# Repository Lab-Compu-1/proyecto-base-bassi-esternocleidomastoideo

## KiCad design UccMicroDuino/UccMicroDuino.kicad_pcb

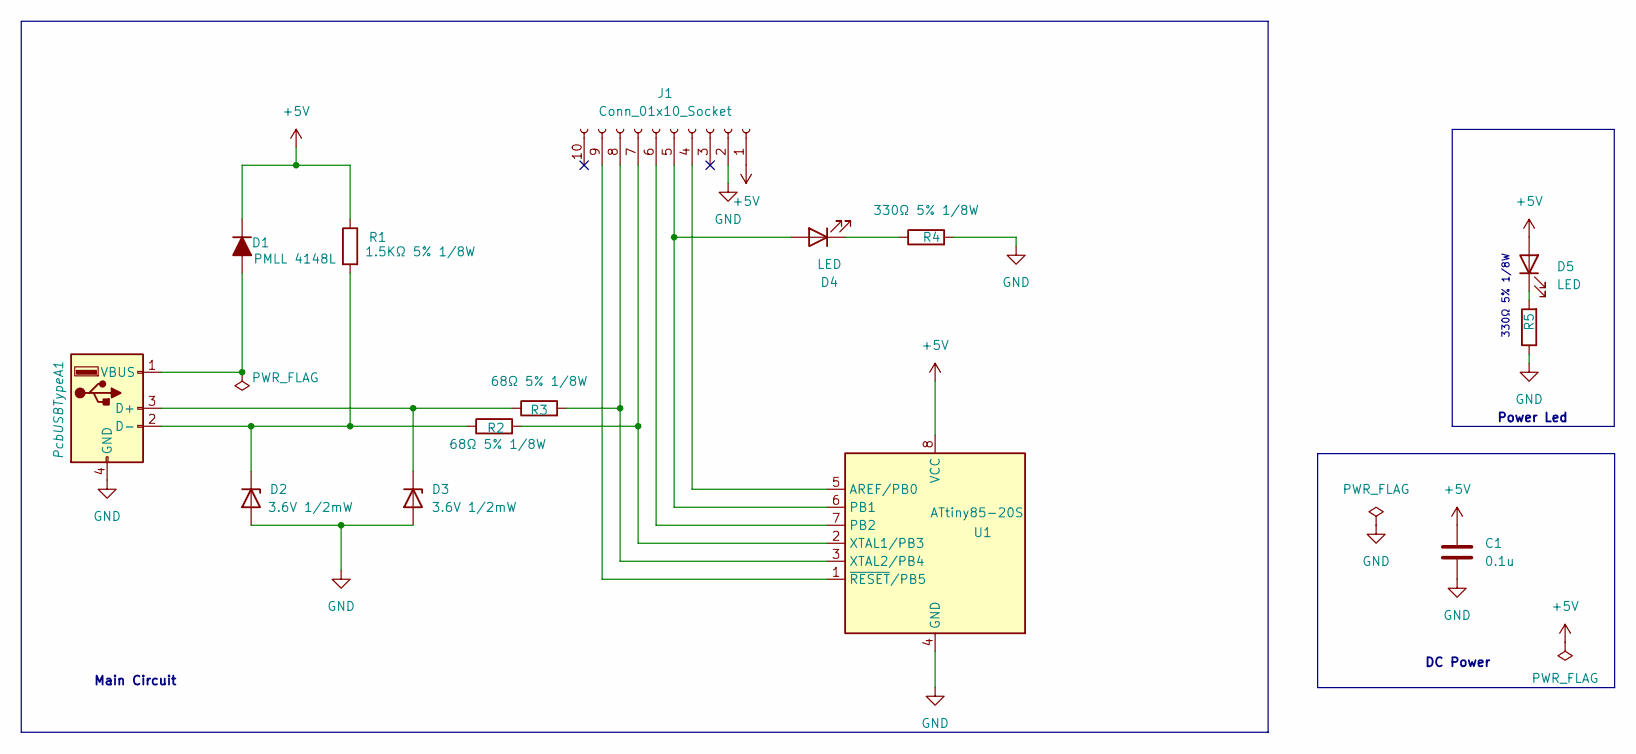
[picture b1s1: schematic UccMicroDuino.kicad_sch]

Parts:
C1: 0.1u; C_0805_2012Metric_Pad1.18x1.45mm_HandSolder
D1: PMLL 4148L; D_MiniMELF
D2, D3: 3.6V 1/2mW; D_SOD-123
D4, D5: LED; ledSMD
J1: Conn_01x10_Socket; PinHeader_1x10_P2.54mm_Vertical
PcbUSBTypeA1: PMLL 4148L; USB_A_UCC
R1: 1.5KΩ 5% 1/8W; R_0805_2012Metric_Pad1.20x1.40mm_HandSolder
R2, R3: 68Ω 5% 1/8W; R_0805_2012Metric_Pad1.20x1.40mm_HandSolder
R4: 330Ω 5% 1/8W; R_0805_2012Metric_Pad1.20x1.40mm_HandSolder
R5: R; R_0805_2012Metric_Pad1.20x1.40mm_HandSolder
U1: ATtiny85-20S; SOIC-8W_5.3x5.3mm_P1.27mm

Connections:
+5V: C1.1, D1.1 (K), D5.2 (A), J1.1, R1.1, U1.8 (VCC)
GND: C1.2, D2.2 (A), D3.2 (A), J1.2, PcbUSBTypeA1.4 (GND), R4.2, R5.1, U1.4 (GND)
unnamed: D1.2 (A), PcbUSBTypeA1.1 (VBUS)
unnamed: D2.1 (K), PcbUSBTypeA1.2 (D-), R1.2, R2.1
unnamed: D3.1 (K), PcbUSBTypeA1.3 (D+), R3.1
unnamed: D4.2 (A), J1.5, U1.6 (PB1)
unnamed: D4.1 (K), R4.1
unnamed: D5.1 (K), R5.2
unnamed: J1.4, U1.5 (AREF/PB0)
unnamed: J1.6, U1.7 (PB2)
unnamed: J1.7, R2.2, U1.2 (XTAL1/PB3)
unnamed: J1.8, R3.2, U1.3 (XTAL2/PB4)
unnamed: J1.9, U1.1 (~RESET/PB5)

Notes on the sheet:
330Ω 5% 1/8W
Main Circuit
Power Led
DC Power

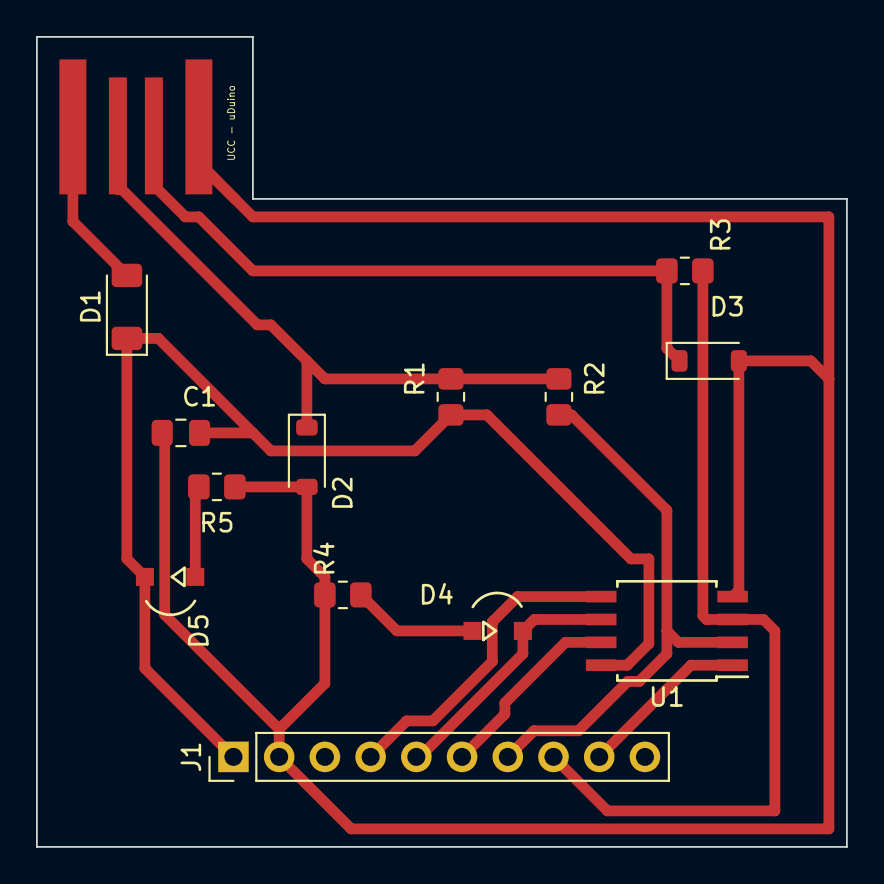
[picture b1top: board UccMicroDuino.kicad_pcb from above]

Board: 2 copper layers, 45.0 x 45.0 mm, 14 parts (0 on the bottom side), 13 nets.

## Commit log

2025-03-17 GitHub Classroom Feedback
2025-03-17 Setting up GitHub Classroom Feedback
